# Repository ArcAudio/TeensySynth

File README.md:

# TeensySynth

Like it says on the tin, it's for the Teensy 4.0 Series. 

I'll put in folder like a normal human when I get round to putting the code up. 

Should just be able to chuck in JLCPCB and get to crack-a-lacking.

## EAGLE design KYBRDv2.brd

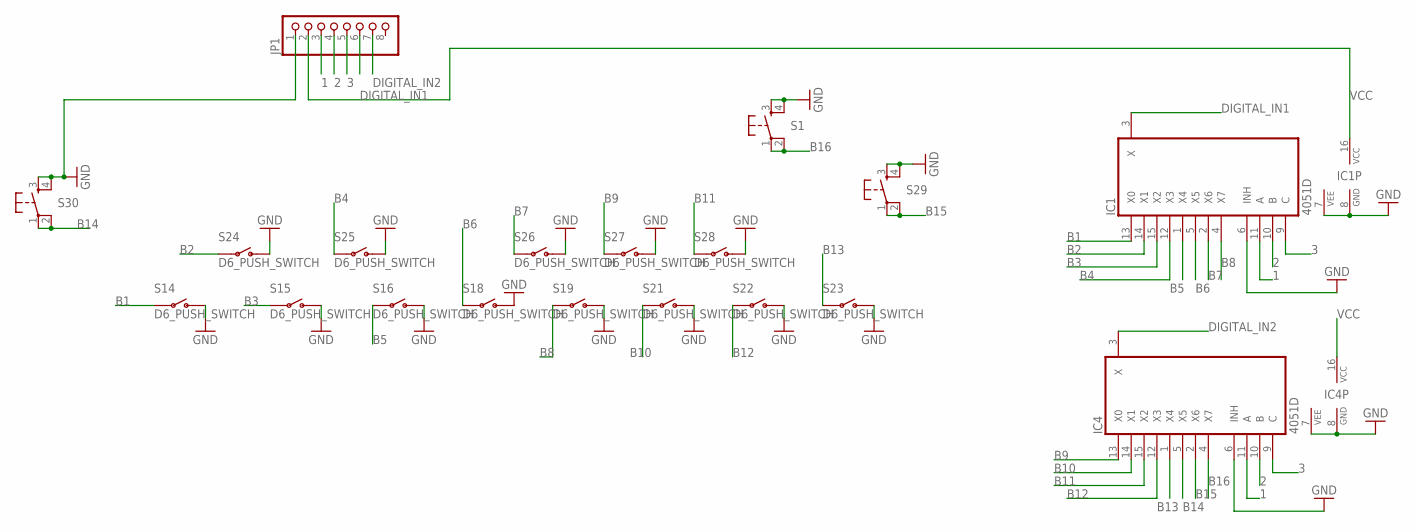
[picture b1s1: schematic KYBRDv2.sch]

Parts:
IC1, IC4: 4051D; SO16
JP1: PINHD-1X8; 1X08
S1, S29, S30: DTSM-6
S14, S15, S16, S18, S19, S21, S22, S23, S24, S25, S26, S27, S28: D6_PUSH_SWITCH

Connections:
1: IC1.11 (A), IC4.11 (A), JP1.3
2: IC1.10 (B), IC4.10 (B), JP1.4
3: IC1.9 (C), IC4.9 (C), JP1.5
B1: IC1.13 (X0), S14.P$3, S14.P$4
B2: IC1.14 (X1), S24.P$3, S24.P$4
B3: IC1.15 (X2), S15.P$3, S15.P$4
B4: IC1.12 (X3), S25.P$3, S25.P$4
B5: IC1.1 (X4), S16.P$3, S16.P$4
B6: IC1.5 (X5), S18.P$3, S18.P$4
B7: IC1.2 (X6), S26.P$3, S26.P$4
B8: IC1.4 (X7), S19.P$3, S19.P$4
B9: IC4.13 (X0), S27.P$3, S27.P$4
B10: IC4.14 (X1), S21.P$3, S21.P$4
B11: IC4.15 (X2), S28.P$3, S28.P$4
B12: IC4.12 (X3), S22.P$3, S22.P$4
B13: IC4.1 (X4), S23.P$3, S23.P$4
B14: IC4.5 (X5), S30.1, S30.2
B15: IC4.2 (X6), S29.1, S29.2
B16: IC4.4 (X7), S1.1, S1.2
DIGITAL_IN1: IC1.3 (X), JP1.6
DIGITAL_IN2: IC4.3 (X), JP1.7
GND: IC1.6 (INH), IC1.7 (VEE), IC1.8 (GND), IC4.6 (INH), IC4.7 (VEE), IC4.8 (GND), JP1.1, S1.3, S1.4, S14.P$1 (O), S14.P$2 (O), S15.P$1 (O), S15.P$2 (O), S16.P$1 (O), S16.P$2 (O), S18.P$1 (O), S18.P$2 (O), S19.P$1 (O), S19.P$2 (O), S21.P$1 (O), S21.P$2 (O), S22.P$1 (O), S22.P$2 (O), S23.P$1 (O), S23.P$2 (O), S24.P$1 (O), S24.P$2 (O), S25.P$1 (O), S25.P$2 (O), S26.P$1 (O), S26.P$2 (O), S27.P$1 (O), S27.P$2 (O), S28.P$1 (O), S28.P$2 (O), S29.3, S29.4, S30.3, S30.4
VCC: IC1.16 (VCC), IC4.16 (VCC), JP1.2

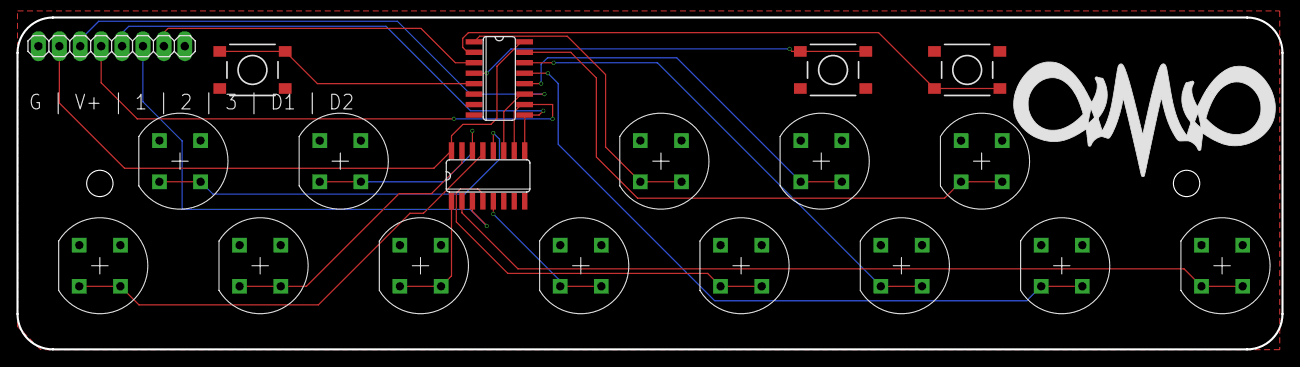
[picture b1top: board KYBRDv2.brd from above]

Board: 2 copper layers, 153.7 x 40.3 mm, 19 parts (0 on the bottom side), 23 nets.

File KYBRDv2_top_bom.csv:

Comment,Designator,Footprint,LCSC Part #
4051D,IC1 IC4,SO16,
DTSM-6,S1 S29 S30,DTSM-6,

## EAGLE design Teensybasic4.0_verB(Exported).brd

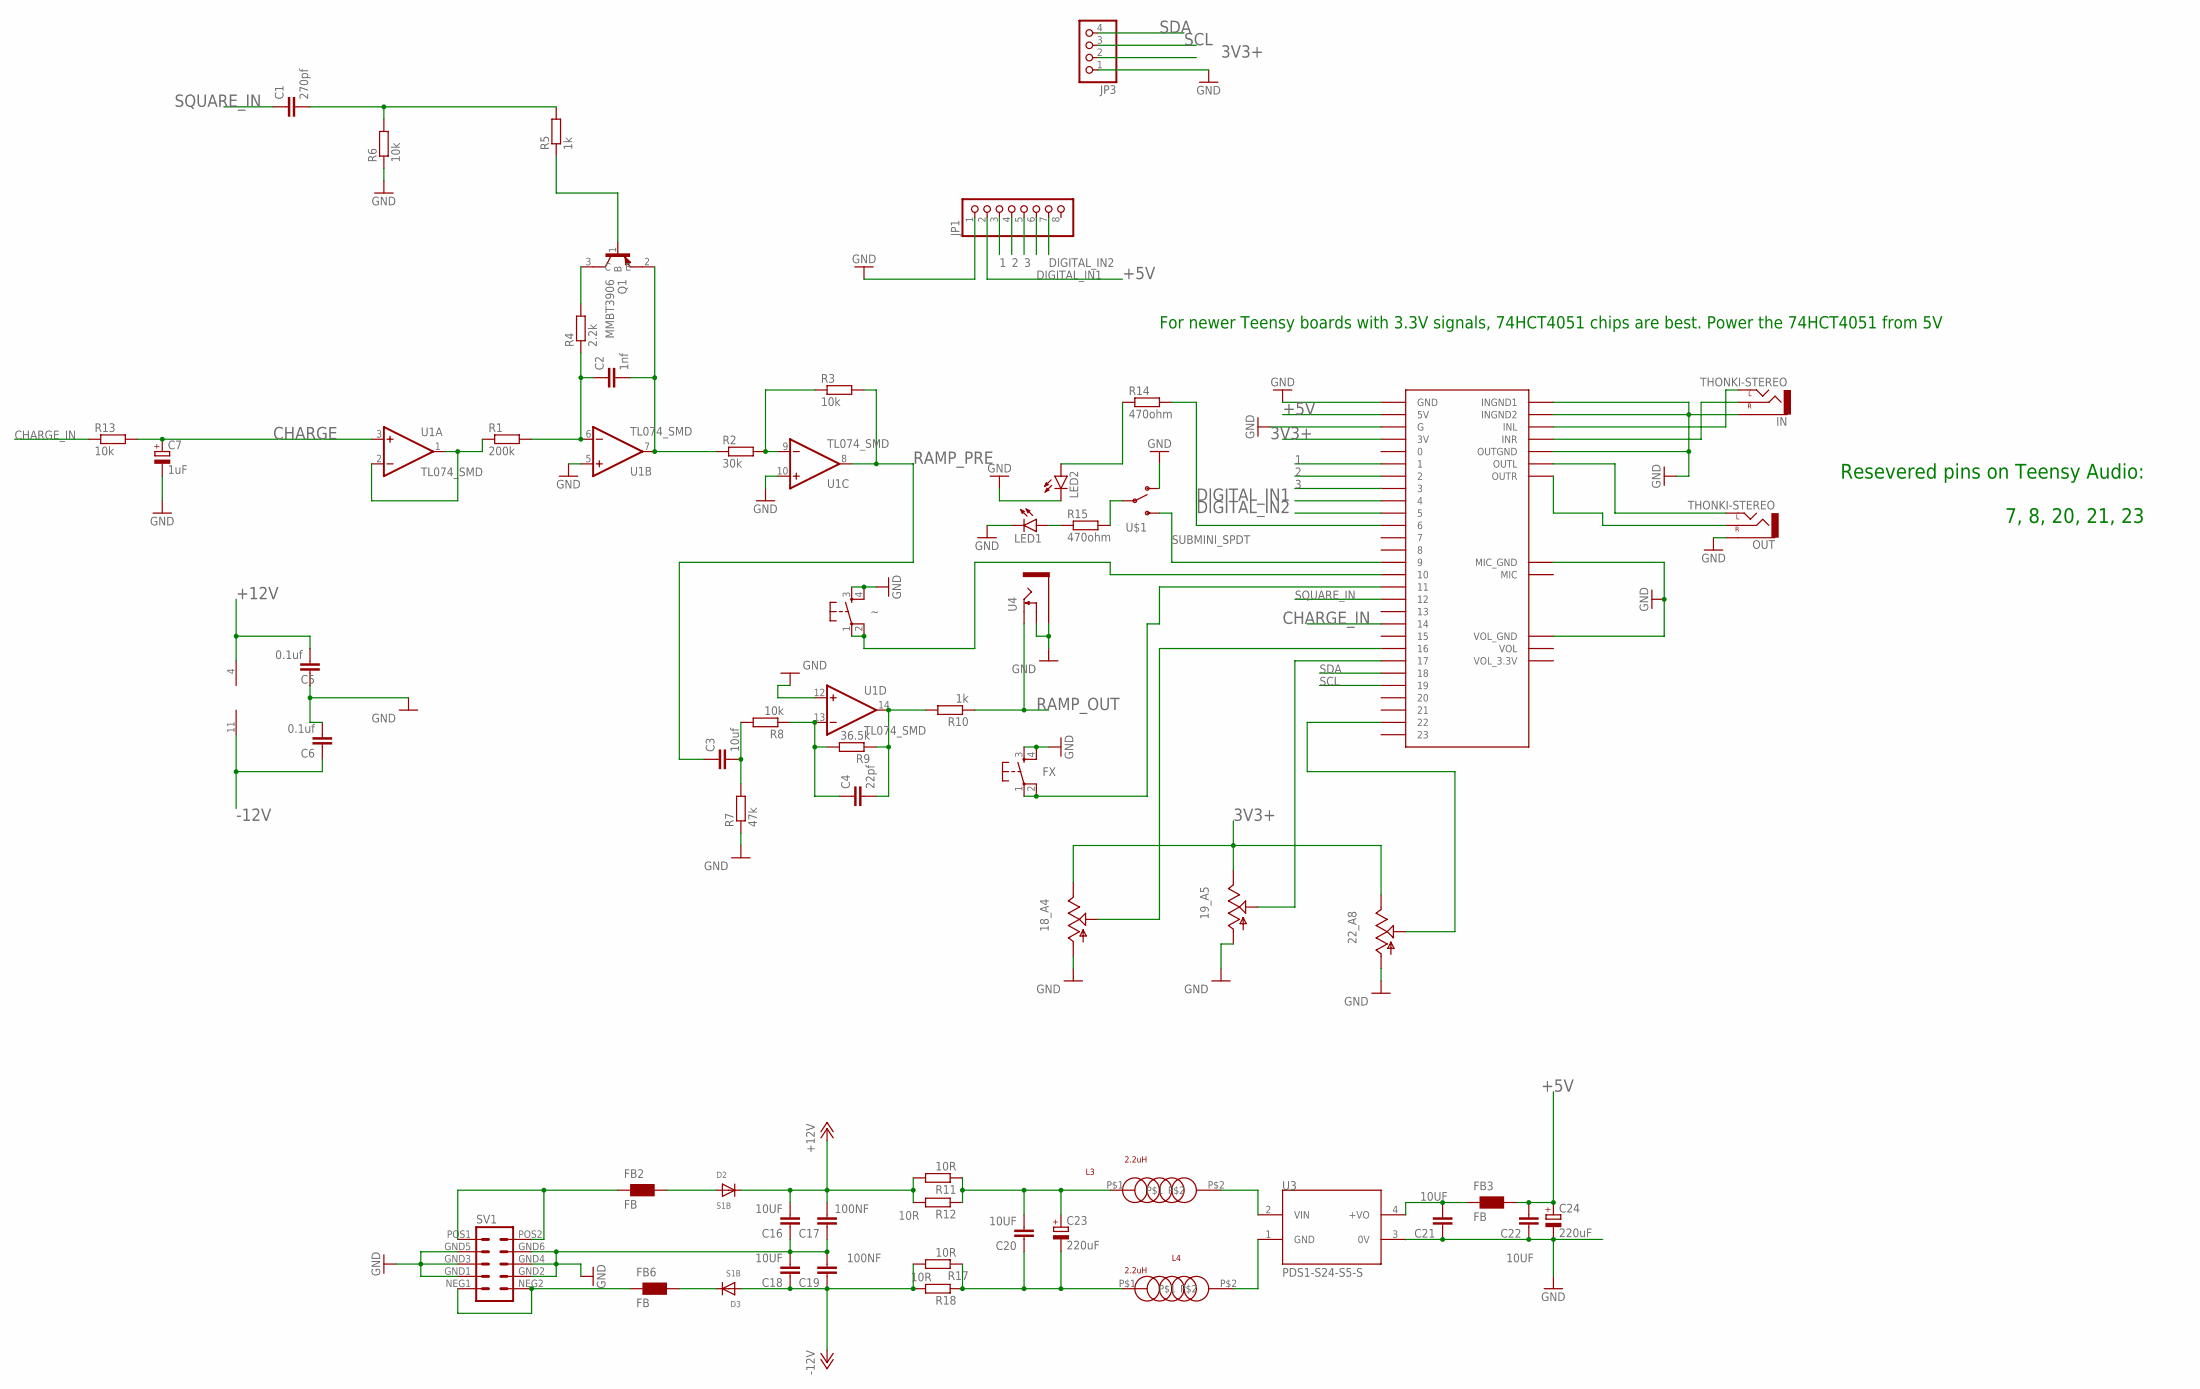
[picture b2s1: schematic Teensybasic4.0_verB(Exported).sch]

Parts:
18_A4, 19_A5, 22_A8: 9MM_SNAP-IN_POT_; 9MM_SNAP-IN_POT
C1: 270pf; C0805
C2: 1nf; C0805
C3: 10uf; C0805
C4: 22pf; C0805
C5, C6: 0.1uf; C0805
C7: 1uF; E2,5-5
C16, C18, C20, C21, C22: 10UF; C0805
C17, C19: 100NF; C0603
C23, C24: 220uF; E2,5-7
D2, D3: S1B; SMADIODE
FB2, FB3, FB6: FB; WUERTH-ELEKTRONIK_0603
FX: DTSM-6
IN: THONKI-STEREO; WQP-PJ366ST_JACK
JP1: PINHD-1X8; 1X08
JP3: PINHD-1X4; 1X04
L3, L4: 2.2uH; 3015_INDUCTOR
LED1, LED2: LED3MM
OUT: THONKI-STEREO; WQP-PJ366ST_JACK
Q1: MMBT3906; SOT95P240X120-3N
R1: 200k; R0805
R2: 30k; R0805
R3, R6, R8, R13: 10k; R0805
R4: 2.2k; R0805
R5, R10: 1k; R0805
R7: 47k; R0805
R9: 36.5k; R0805
R11, R12, R17, R18: 10R; R0603
R14, R15: 470ohm; R0805
SV1: EURO_POWER_HEADERLOCK_PADS; EURO_PWR_HEADER_LOCK
U1: TL074_SMD; SO14
U3: PDS1-S24-S5-S; CONV_PDS1-S24-S5-S
U4: THONKICONNNEW; WQP-PJ301M-12_JACK
U$1: SUBMINI_SPDT; SUBMINI_TOGGLE
U$2: AUDIOSHIELD
~: DTSM-6

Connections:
1: JP1.3, U$2.1
2: JP1.4, U$2.2
3: JP1.5, U$2.3
3V3+: 18_A4.3 (E), 19_A5.3 (E), 22_A8.3 (E), JP3.2, U$2.3V
+5V: C22.2, C24.+, FB3.2, JP1.2, U$2.5V
+12V: C5.2, C16.2, C17.2, D2.C, R11.2, R12.2, U1.4 (V+)
-12V: C6.1, C18.1, C19.1, D3.A, R17.2, R18.2, U1.11 (V-)
CHARGE: C7.+, R13.2, U1.3 (+IN)
CHARGE_IN: R13.1, U$2.14
DIGITAL_IN1: JP1.6, U$2.4
DIGITAL_IN2: JP1.7, U$2.5
GND: 18_A4.1 (A), 19_A5.1 (A), 22_A8.1 (A), C5.1, C6.2, C7.-, C16.1, C17.1, C18.2, C19.2, C21.1, C22.1, C24.-, FX.3, FX.4, IN.P$3_SLEEVE (SLEEVE), JP1.1, JP3.1, LED1.K (C), LED2.K (C), OUT.P$3_SLEEVE (SLEEVE), R6.1, R7.1, SV1.GND1 (4), SV1.GND2 (3), SV1.GND3 (6), SV1.GND4 (5), SV1.GND5 (8), SV1.GND6 (7), U1.5 (+IN), U1.10 (+IN), U1.12 (+IN), U3.3 (0V), U4.P$2_SWITCH (SWITCH), U4.P$3_SLEEVE (SLEEVE), U$1.1 (O), U$2.G, U$2.GND, U$2.GND_MIC (MIC_GND), U$2.INGND1, U$2.INGND2, U$2.OUTGND, U$2.VOL_GND, ~.3, ~.4
unnamed: R1.1, U1.1 (OUT), U1.2 (-IN)
unnamed: Q1.3 (C), R4.2
unnamed: C4.1, R8.1, R9.2, U1.13 (-IN)
unnamed: C2.1, R1.2, R4.1, U1.6 (-IN)
unnamed: C2.2, Q1.2 (E), R2.1, U1.7 (OUT)
unnamed: Q1.1 (B), R5.1
unnamed: C1.2, R5.2, R6.2
unnamed: C4.2, R9.1, R10.2, U1.14 (OUT)
unnamed: R2.2, R3.1, U1.9 (-IN)
unnamed: C3.2, R7.2, R8.2
unnamed: U$1.3 (S), U$2.9
unnamed: IN.P$1_TIP (LEFT), U$2.INL
unnamed: R15.2, U$1.COM (COMMON)
unnamed: LED1.A, R15.1
unnamed: U$2.10, ~.1, ~.2
unnamed: FX.1, FX.2, U$2.11
unnamed: IN.P$2_SWITCH (RIGHT), U$2.INR
unnamed: OUT.P$1_TIP (LEFT), U$2.OUTL
unnamed: OUT.P$2_SWITCH (RIGHT), U$2.OUTR
unnamed: LED2.A, R14.1
unnamed: 19_A5.2 (S), U$2.17
unnamed: 18_A4.2 (S), U$2.16
unnamed: 22_A8.2 (S), U$2.22
unnamed: R14.2, U$2.6
unnamed: FB6.1, SV1.NEG1 (2), SV1.NEG2 (1)
unnamed: FB2.1, SV1.POS1 (10), SV1.POS2 (9)
unnamed: C20.2, C23.+, L3.P$1, R11.1, R12.1
unnamed: C20.1, C23.-, L4.P$1, R17.1, R18.1
unnamed: C21.2, FB3.1, U3.4 (+VO)
unnamed: L3.P$2, U3.2 (VIN)
unnamed: L4.P$2, U3.1 (GND)
unnamed: D2.A, FB2.2
unnamed: D3.C, FB6.2
RAMP_OUT: R10.1, U4.P$1_TIP (TIP)
RAMP_PRE: C3.1, R3.2, U1.8 (OUT)
SCL: JP3.3, U$2.19
SDA: JP3.4, U$2.18
SQUARE_IN: C1.1, U$2.12

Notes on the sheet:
Resevered pins on Teensy Audio: 7, 8, 20, 21, 23
For newer Teensy boards with 3.3V signals, 74HCT4051 chips are best. Power the 74HCT4051 from 5V

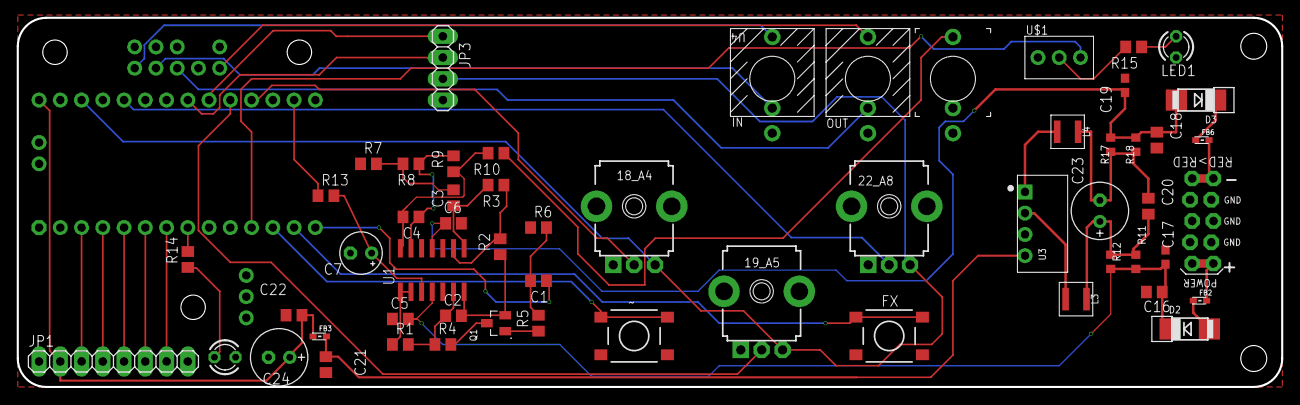
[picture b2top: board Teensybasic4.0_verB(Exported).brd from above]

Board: 2 copper layers, 151.1 x 44.1 mm, 58 parts (0 on the bottom side), 50 nets.

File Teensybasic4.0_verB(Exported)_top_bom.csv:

Comment,Designator,Footprint,LCSC Part #
0.1uf,C5 C6,C0805,
1k,R5 R10,R0805,
1nf,C2,C0805,
2.2k,R4,R0805,
2.2uH,L3 L4,3015_INDUCTOR,
10R,R11 R12 R17 R18,R0603,
10UF,C16 C18 C20 C21 C22,C0805,
10k,R3 R6 R8 R13,R0805,
10uf,C3,C0805,
22pf,C4,C0805,
30k,R2,R0805,
36.5k,R9,R0805,
47k,R7,R0805,
100NF,C17 C19,C0603,
200k,R1,R0805,
270pf,C1,C0805,
470ohm,R14 R15,R0805,
DTSM-6,FX ~,DTSM-6,
FB,FB2 FB3 FB6,WUERTH-ELEKTRONIK_0603,
MMBT3906,Q1,SOT95P240X120-3N,
S1B,D2 D3,SMADIODE,
TL074_SMD,U1,SO14,

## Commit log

2021-04-04 Hardware
2021-04-04 CAM files
2021-04-04 This is a weird place to write something
